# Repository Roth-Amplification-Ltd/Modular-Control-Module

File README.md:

# Modular-Control-Module
Modular-Control-Module or MCM is the Encoder + Button board inside all Roth Amplification pedals.

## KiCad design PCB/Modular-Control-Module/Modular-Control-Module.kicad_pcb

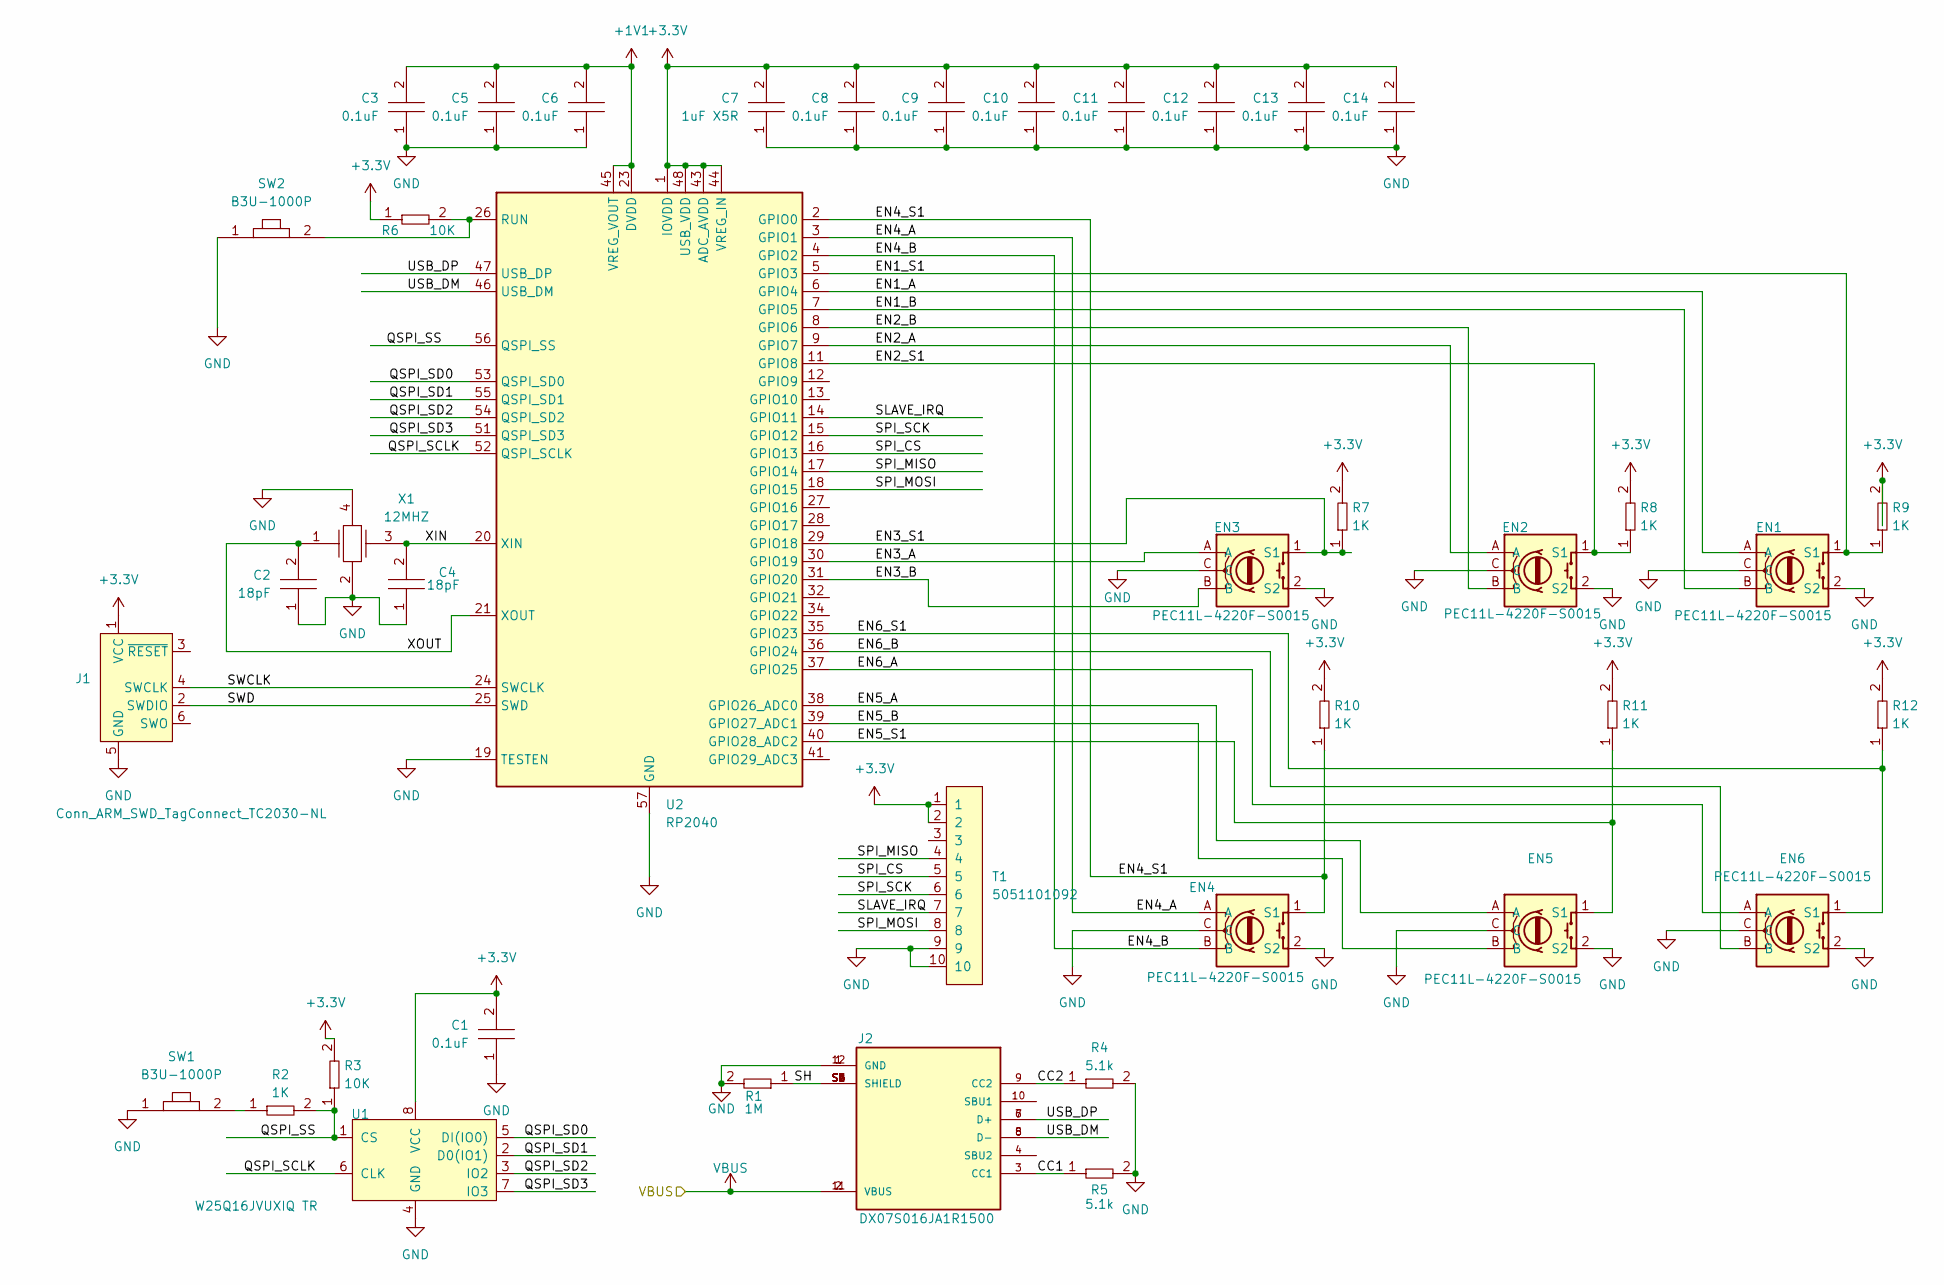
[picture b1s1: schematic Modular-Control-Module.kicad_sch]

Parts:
C1, C3, C5, C6, C8, C9, C10, C11, C12, C13, C14: C0402C104K9PACTU; R0402; Tolerance 10%; Voltage 6.3V; MFR# C0402C104K9PACTU
C2, C4: GCM1555C1H180GA16D; C0402; Tolerance 2%; Voltage 50V; MFR# GCM1555C1H180GA16D
C7: CC0603KRX5R7BB105; C0603; Tolerance 10%; Voltage 16V; MFR# CC0603KRX5R7BB105
EN1, EN2, EN3, EN4, EN5, EN6: PEC11L-4220F-S0015; PEC11L-4xxxF-Sxxxx_BRN; Tolerance N/A; Voltage N/A; MFR# PEC11L-4220F-S0015
J1: Conn_ARM_SWD_TagConnect_TC2030-NL; Tag-Connect_TC2030-IDC-NL_2x03_P1.27mm_Vertical
J2: DX07S016JA1R1500; JAE_DX07S016JA1R1500; Tolerance *; Voltage 20V; MFR# DX07S016JA1R1500
R1: RT0603BRD071ML; R0603; Tolerance 1%; Voltage N/A; MFR# RT0603BRD071ML
R2, R7, R8, R9, R10, R11, R12: RC0402FR-071KL; R0402; Tolerance 1%; Voltage *; MFR# RC0402FR-071KL
R3, R6: RC0402FR-0710KL; R0402; Tolerance 1%; Voltage *; MFR# RC0402FR-0710KL
R4, R5: RC0402FR-075K1L; R0402; Tolerance 1%; Voltage N/A; MFR# RC0402FR-075K1L
SW1, SW2: B3U-1000P; Tolerance *; Voltage *; MFR# B3U-1000P
T1: 5051101092; CON_5051101092_MOL; Tolerance *; Voltage 50V; MFR# 5051101092
U1: TEMPLATE; PSON50P300X200X60-9N; Tolerance *; Voltage 3.3V; MFR# W25Q16JVUXIQ TR
U2: RP2040; QFN-56-1EP_7x7mm_P0.4mm_EP3.2x3.2mm
X1: ABM8G-12.000MHZ-18-D2Y-T; XTAL_ABM8G-12.000MHZ-18-D2Y-T; Tolerance ±20ppm; Voltage *; MFR# ABM8G-12.000MHZ-18-D2Y-T

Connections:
+1V1: C3.2, C5.2, C6.2, U2.23 (DVDD), U2.45 (VREG_VOUT), U2.50 (DVDD)
+3.3V: C1.2, C7.2, C8.2, C9.2, C10.2, C11.2, C12.2, C13.2, C14.2, J1.1 (VCC), R3.2, R6.1, R7.2, R8.2, R9.2, R10.2, R11.2, R12.2, T1.1, T1.2, U1.8 (VCC), U2.1 (IOVDD), U2.10 (IOVDD), U2.22 (IOVDD), U2.33 (IOVDD), U2.42 (IOVDD), U2.43 (ADC_AVDD), U2.44 (VREG_IN), U2.48 (USB_VDD), U2.49 (IOVDD)
/CC1: J2.3 (CC1), R5.1
/CC2: J2.9 (CC2), R4.1
/EN1_A: EN1.A, U2.6 (GPIO4)
/EN1_B: EN1.B, U2.7 (GPIO5)
/EN1_S1: EN1.1 (S1), R9.1, U2.5 (GPIO3)
/EN2_A: EN2.A, U2.9 (GPIO7)
/EN2_B: EN2.B, U2.8 (GPIO6)
/EN2_S1: EN2.1 (S1), R8.1, U2.11 (GPIO8)
/EN3_A: EN3.A, U2.30 (GPIO19)
/EN3_B: EN3.B, U2.31 (GPIO20)
/EN3_S1: EN3.1 (S1), R7.1, U2.29 (GPIO18)
/EN4_A: EN4.A, U2.3 (GPIO1)
/EN4_B: EN4.B, U2.4 (GPIO2)
/EN4_S1: EN4.1 (S1), R10.1, U2.2 (GPIO0)
/EN5_A: EN5.A, U2.38 (GPIO26_ADC0)
/EN5_B: EN5.B, U2.39 (GPIO27_ADC1)
/EN5_S1: EN5.1 (S1), R11.1, U2.40 (GPIO28_ADC2)
/EN6_A: EN6.A, U2.37 (GPIO25)
/EN6_B: EN6.B, U2.36 (GPIO24)
/EN6_S1: EN6.1 (S1), R12.1, U2.35 (GPIO23)
/QSPI_SCLK: U1.6 (CLK), U2.52 (QSPI_SCLK)
/QSPI_SD0: U1.5 (DI(IO0)), U2.53 (QSPI_SD0)
/QSPI_SD1: U1.2 (D0(IO1)), U2.55 (QSPI_SD1)
/QSPI_SD2: U1.3 (IO2), U2.54 (QSPI_SD2)
/QSPI_SD3: U1.7 (IO3), U2.51 (QSPI_SD3)
/QSPI_SS: R2.2, R3.1, U1.1 (CS), U2.56 (QSPI_SS)
/SH: J2.S1 (SHIELD), J2.S2 (SHIELD), J2.S3 (SHIELD), J2.S4 (SHIELD), J2.S5 (SHIELD), J2.S6 (SHIELD), R1.1
/SLAVE_IRQ: T1.7, U2.14 (GPIO11)
/SPI_CS: T1.5, U2.16 (GPIO13)
/SPI_MISO: T1.4, U2.17 (GPIO14)
/SPI_MOSI: T1.8, U2.18 (GPIO15)
/SPI_SCK: T1.6, U2.15 (GPIO12)
/SWCLK: J1.4 (SWCLK), U2.24 (SWCLK)
/SWD: J1.2 (SWDIO), U2.25 (SWD)
/USB_DM: J2.5 (D-), J2.8 (D-), U2.46 (USB_DM)
/USB_DP: J2.6 (D+), J2.7 (D+), U2.47 (USB_DP)
/XIN: C4.2, U2.20 (XIN), X1.3
/XOUT: C2.2, U2.21 (XOUT), X1.1
GND: C1.1, C2.1, C3.1, C4.1, C5.1, C6.1, C7.1, C8.1, C9.1, C10.1, C11.1, C12.1, C13.1, C14.1, EN1.2 (S2), EN1.C, EN2.2 (S2), EN2.C, EN3.2 (S2), EN3.C, EN4.2 (S2), EN4.C, EN5.2 (S2), EN5.C, EN6.2 (S2), EN6.C, J1.5 (GND), J2.1 (GND), J2.12 (GND), R1.2, R4.2, R5.2, SW1.1, SW2.1, T1.9, T1.10, U1.4 (GND), U2.19 (TESTEN), U2.57 (GND), X1.2, X1.4
unnamed: R2.1, SW1.2
unnamed: R6.2, SW2.2, U2.26 (RUN)
VBUS: J2.2 (VBUS), J2.11 (VBUS)

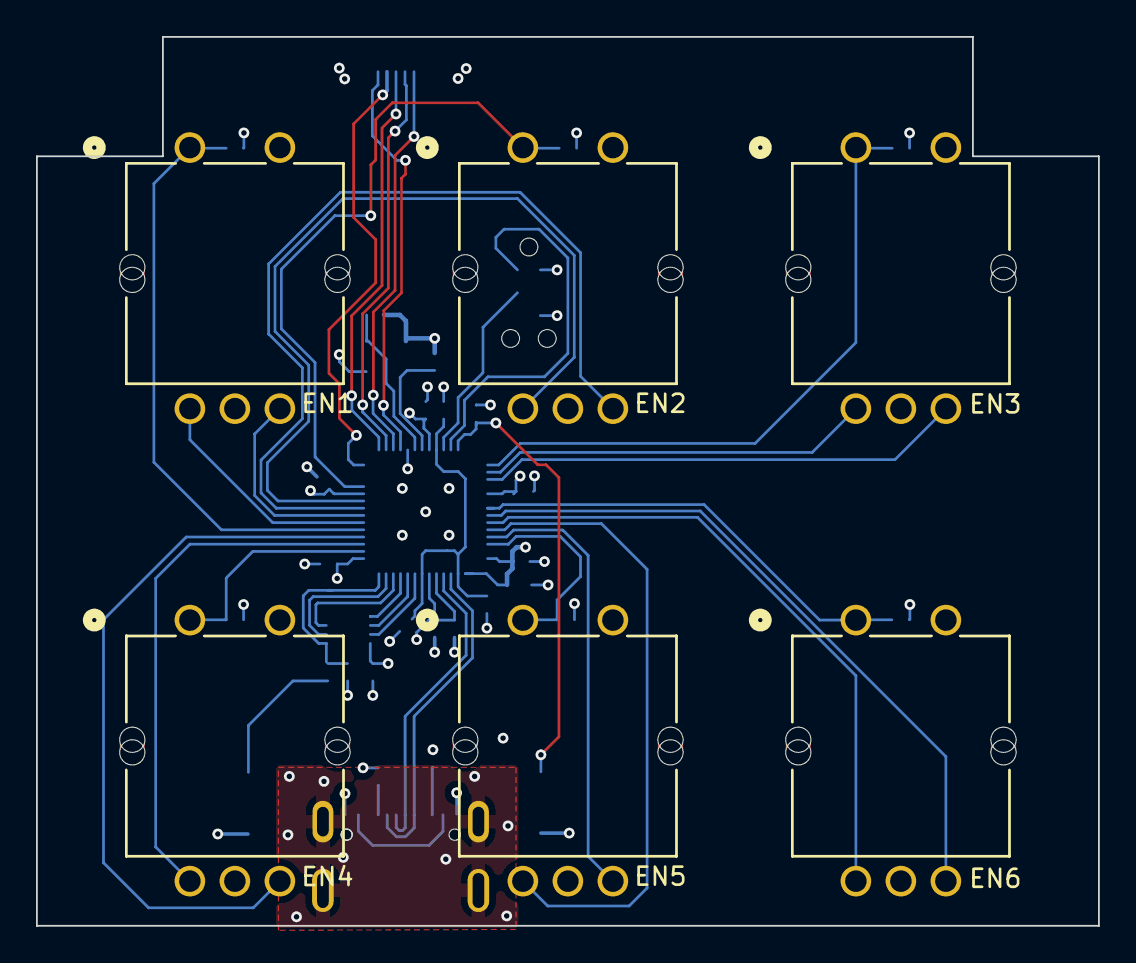
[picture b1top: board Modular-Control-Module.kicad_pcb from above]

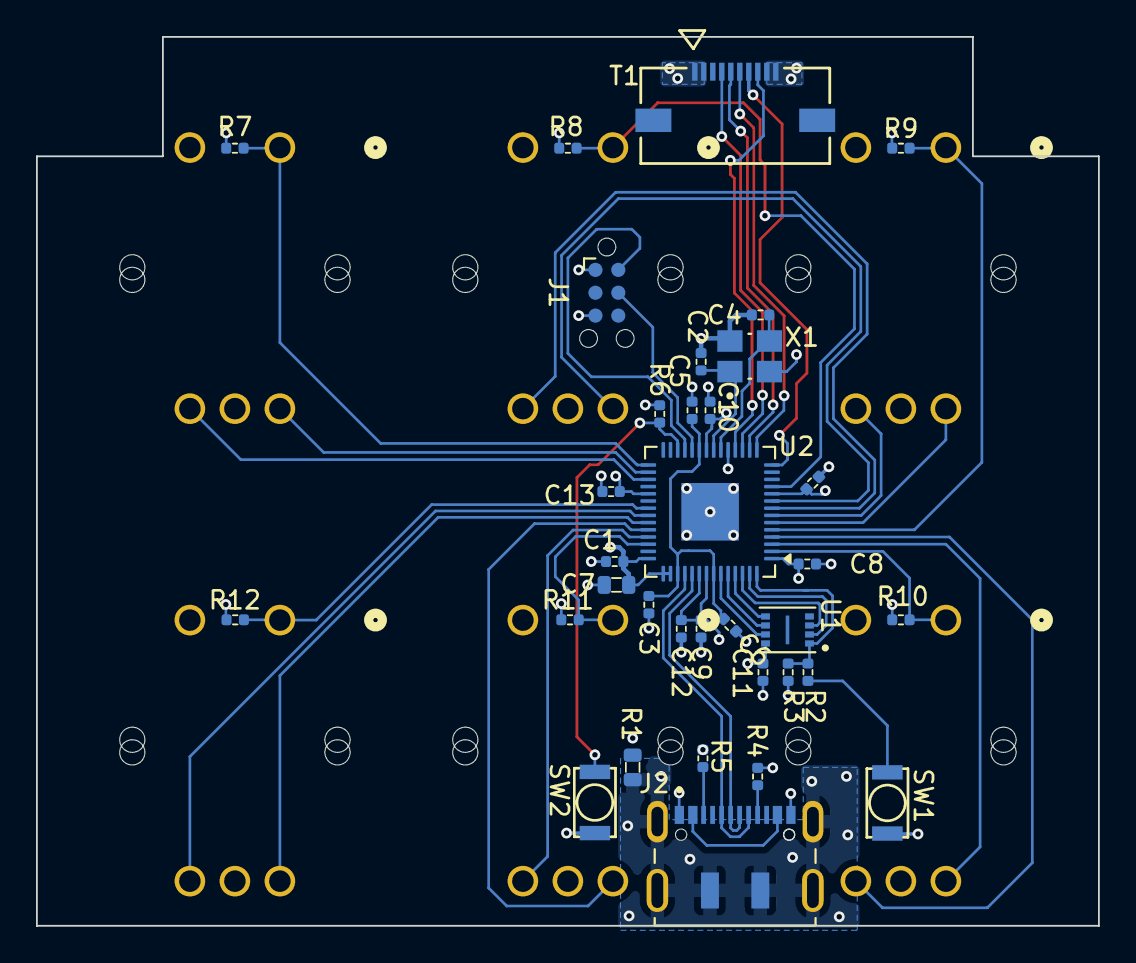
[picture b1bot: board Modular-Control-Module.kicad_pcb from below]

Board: 4 copper layers, 59.0 x 49.4 mm, 40 parts (34 on the bottom side), 44 nets.

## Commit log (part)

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2026-02-04 Project created
    Project created from original encoder carrier. Schematic updated with RP2040 circuit and connections rewroted. PCB in progress.
2026-02-18 WIP save
    WIP save gonna try flipping the MCU around.
2026-02-18 Flip Worked
    Flipping MCU 90 degrees worked, PCB redesigned around that topology, connector for main board added.
2026-04-29 Add CERN Open Hardware Licence
    Added CERN Open Hardware Licence Version 2 - Strongly Reciprocal to the project.
